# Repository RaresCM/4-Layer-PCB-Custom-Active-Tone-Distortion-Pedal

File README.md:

# Custom 4 Layer PCB Active Tone Distortion Pedal
Custom distortion pedal design aiming to apply theoretical knowledge from my EEE course to a real life project. Designed from the ground up from schematic to PCB to 3D model by me.

Implements my EEE course theory on filters, op-amps, power delivery and analog circuits.

## Specifications:
- 4 Layer PCB with a dedicated ground copper pour plane, power plane and 2 signal planes
- Dual 9V power input from a battery or barrel jack with ±9V delivery using a charge pump
- 3 Op-Amp design using a TL081 for gain and 2 NE5532 for volume output and 3 tone active tone stack
- De-coupling capacitors for stable op amp operation and a low pass filter input for noise elimination
- Designed in KiCad 10.0

## Repository Structure
- /manufacturing - KiCad generated gerber and manufacturing files
- /Distortion Pedal - KiCad files for the schematic, PCB layout, 3D model etc.
- /designlog - My design decisions and what could be improved

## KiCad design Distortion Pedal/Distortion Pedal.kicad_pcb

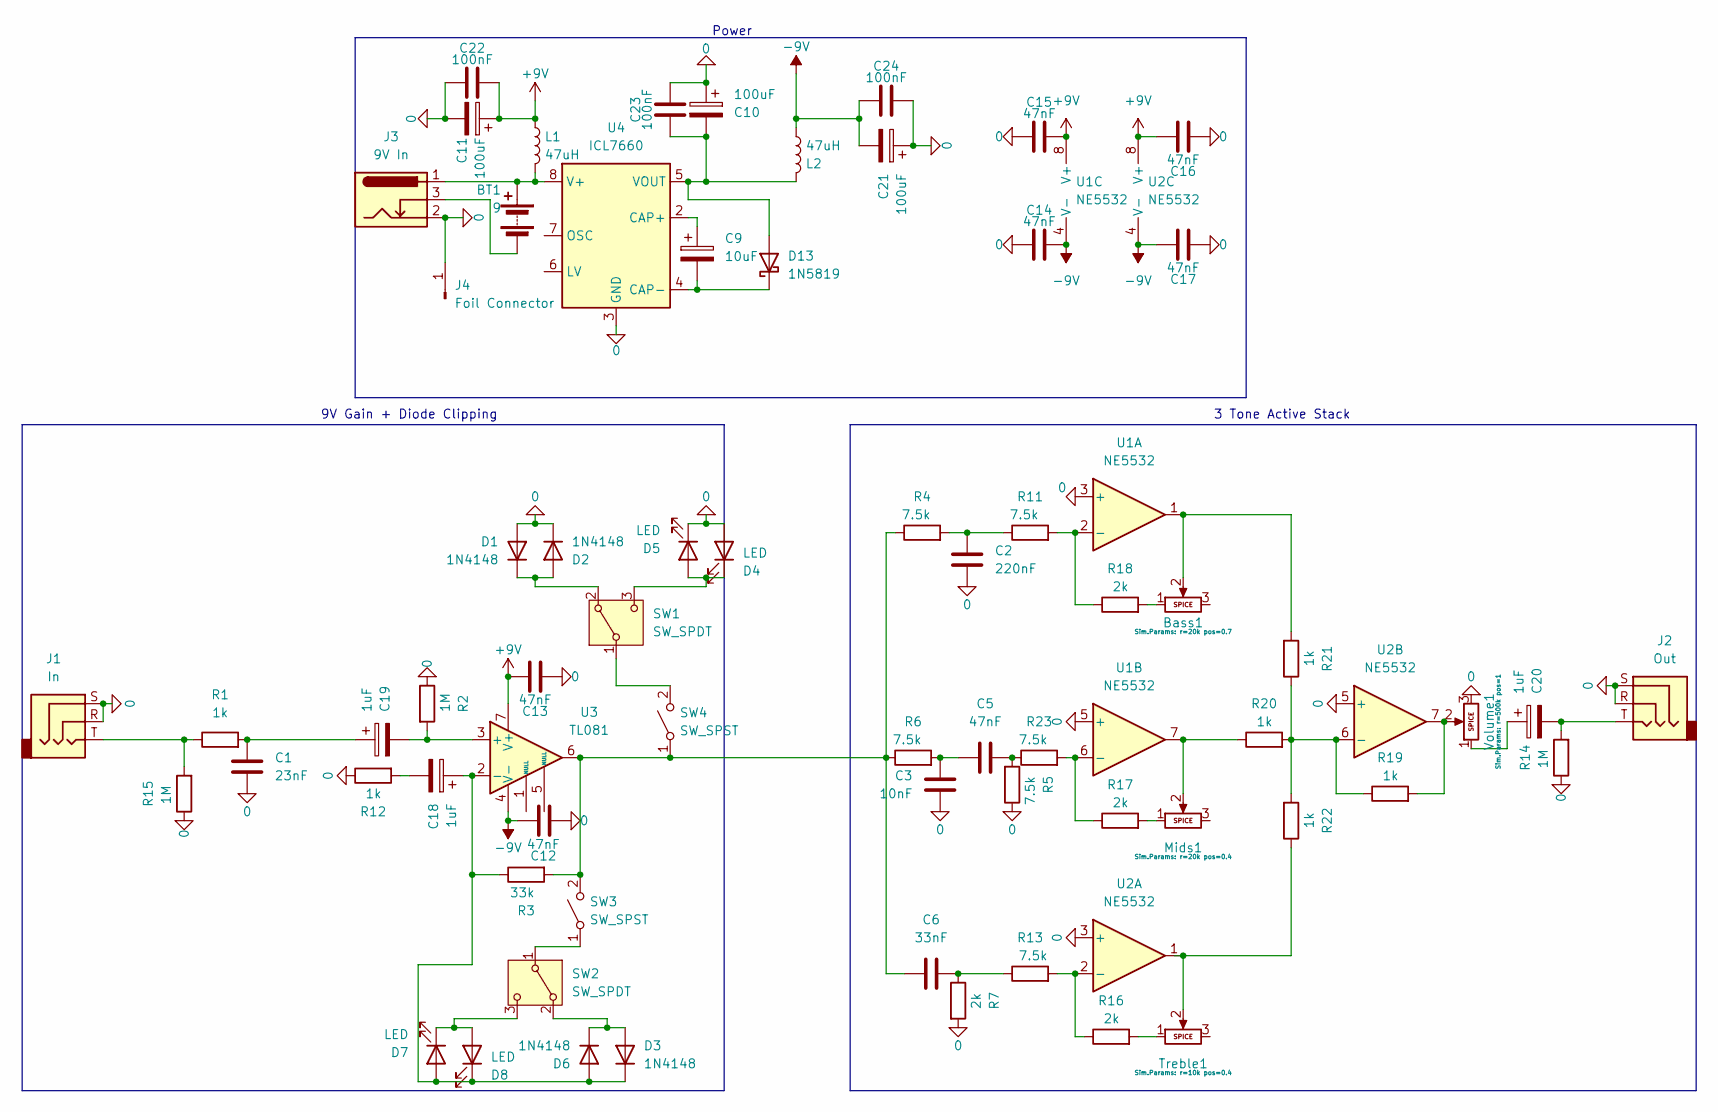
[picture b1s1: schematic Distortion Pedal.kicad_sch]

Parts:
BT1: 9; BatteryHolder_Eagle_12BH611-GR
Bass1: Potentiometer; Potentiometer_ACP_CA14V-15_Vertical
C1: 23nF; C_Disc_D11.0mm_W5.0mm_P7.50mm
C2: 220nF; C_Disc_D11.0mm_W5.0mm_P7.50mm
C3: 10nF; C_Disc_D11.0mm_W5.0mm_P7.50mm
C5, C12, C13, C14, C15, C16, C17: 47nF; C_Disc_D11.0mm_W5.0mm_P7.50mm
C6: 33nF; C_Disc_D11.0mm_W5.0mm_P7.50mm
C9: 10uF; CP_Radial_D14.0mm_P7.50mm
C10, C11, C21: 100uF; CP_Radial_D13.0mm_P7.50mm
C18, C19: 1uF; CP_Radial_D13.0mm_P7.50mm
C20: 1uF; CP_Radial_D14.0mm_P7.50mm
C22, C23, C24: 100nF; C_Disc_D11.0mm_W5.0mm_P7.50mm
D1, D2, D3, D6: 1N4148; D_DO-35_SOD27_P7.62mm_Horizontal
D4, D5, D7, D8: LED; LED_D5.0mm_FlatTop
D13: 1N5819; D_DO-41_SOD81_P10.16mm_Horizontal
J1: In; Jack_6.35mm_Neutrik_NJ3FD-V_Vertical
J2: Out; Jack_6.35mm_Neutrik_NJ3FD-V_Vertical
J3: 9V In; BarrelJack_GCT_DCJ200-10-A_Horizontal
J4: Foil Connector; PinHeader_1x01_P1.00mm_Vertical
L1, L2: 47uH; L_Radial_D12.0mm_P6.00mm_Murata_1900R
Mids1: Potentiometer; Potentiometer_ACP_CA14V-15_Vertical
R1, R12, R19, R20, R21, R22: 1k; R_Axial_DIN0204_L3.6mm_D1.6mm_P5.08mm_Horizontal
R2, R14, R15: 1M; R_Axial_DIN0204_L3.6mm_D1.6mm_P5.08mm_Horizontal
R3: 33k; R_Axial_DIN0204_L3.6mm_D1.6mm_P5.08mm_Horizontal
R4, R5, R6, R11, R13, R23: 7.5k; R_Axial_DIN0204_L3.6mm_D1.6mm_P5.08mm_Horizontal
R7, R16, R17, R18: 2k; R_Axial_DIN0204_L3.6mm_D1.6mm_P5.08mm_Horizontal
SW1, SW2: SW_SPDT; SW_Slide-03_Wuerth-WS-SLTV_10x2.5x6.4_P2.54mm
SW3, SW4: SW_SPST; SW_PUSH_1P1T_6x3.5mm_H5.0_APEM_MJTP1250
Treble1: Potentiometer; Potentiometer_ACP_CA14V-15_Vertical
U1, U2: NE5532; DIP-8_W7.62mm
U3: TL081; DIP-8_W7.62mm
U4: ICL7660; DIP-8_W7.62mm
Volume1: Potentiometer; Potentiometer_ACP_CA14V-15_Vertical

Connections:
0: C1.1, C2.1, C3.2, C10.1, C11.2, C12.2, C13.2, C14.2, C15.2, C16.2, C17.2, C21.1, C22.2, C23.1, C24.1, D1.2 (A), D2.1 (K), D4.2 (A), D5.1 (K), J1.R, J1.S, J2.R, J2.S, J3.2, J4.1 (Pin_1_1), R2.1, R5.1, R7.2, R12.1, R14.1, R15.1, U1.3 (+), U1.5 (+), U2.3 (+), U2.5 (+), U4.3 (GND), Volume1.3
+9V: C11.1, C13.1, C15.1, C16.1, C22.1, L1.1, U1.8 (V+), U2.8 (V+), U3.7 (V+)
-9V: C12.1, C14.1, C17.1, C21.2, C24.2, L2.2, U1.4 (V-), U2.4 (V-), U3.4 (V-)
unnamed: BT1.1 (+), J3.1, L1.2, U4.8 (V+)
unnamed: BT1.2 (-), J3.3
unnamed: Bass1.1, R18.2
unnamed: Bass1.2, R21.2, U1.1
unnamed: C1.2, C19.1, R1.2
unnamed: C2.2, R4.2, R11.1
unnamed: C3.1, C5.2, R6.2
unnamed: C5.1, R5.2, R23.1
unnamed: C6.1, R7.1, R13.1
unnamed: C18.2, R12.2
unnamed: C20.1, Volume1.1
unnamed: C20.2, J2.T, R14.2
unnamed: D1.1 (K), D2.2 (A), SW1.2 (B)
unnamed: D3.2 (A), D6.1 (K), SW2.2 (B)
unnamed: C18.1, D3.1 (K), D6.2 (A), D7.2 (A), D8.1 (K), R3.1, U3.2 (-)
unnamed: D4.1 (K), D5.2 (A), SW1.3 (C)
unnamed: D7.1 (K), D8.2 (A), SW2.3 (C)
unnamed: C10.2, C23.2, D13.2 (A), L2.1, U4.5 (VOUT)
unnamed: C9.2, D13.1 (K), U4.4 (CAP-)
unnamed: J1.T, R1.1, R15.2
unnamed: Mids1.1, R17.2
unnamed: Mids1.2, R20.1, U1.7
unnamed: R16.2, Treble1.1
unnamed: R19.2, U2.7, Volume1.2
unnamed: R22.1, Treble1.2, U2.1
unnamed: SW1.1 (A), SW4.2 (B)
unnamed: SW2.1 (A), SW3.1 (A)
unnamed: C6.2, R3.2, R4.1, R6.1, SW3.2 (B), SW4.1 (A), U3.6
unnamed: R11.2, R18.1, U1.2 (-)
unnamed: R17.1, R23.2, U1.6 (-)
unnamed: R13.2, R16.1, U2.2 (-)
unnamed: R19.1, R20.2, R21.1, R22.2, U2.6 (-)
unnamed: C19.2, R2.2, U3.3 (+)
unnamed: C9.1, U4.2 (CAP+)

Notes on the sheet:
3 Tone Active Stack
Power
9V Gain + Diode Clipping

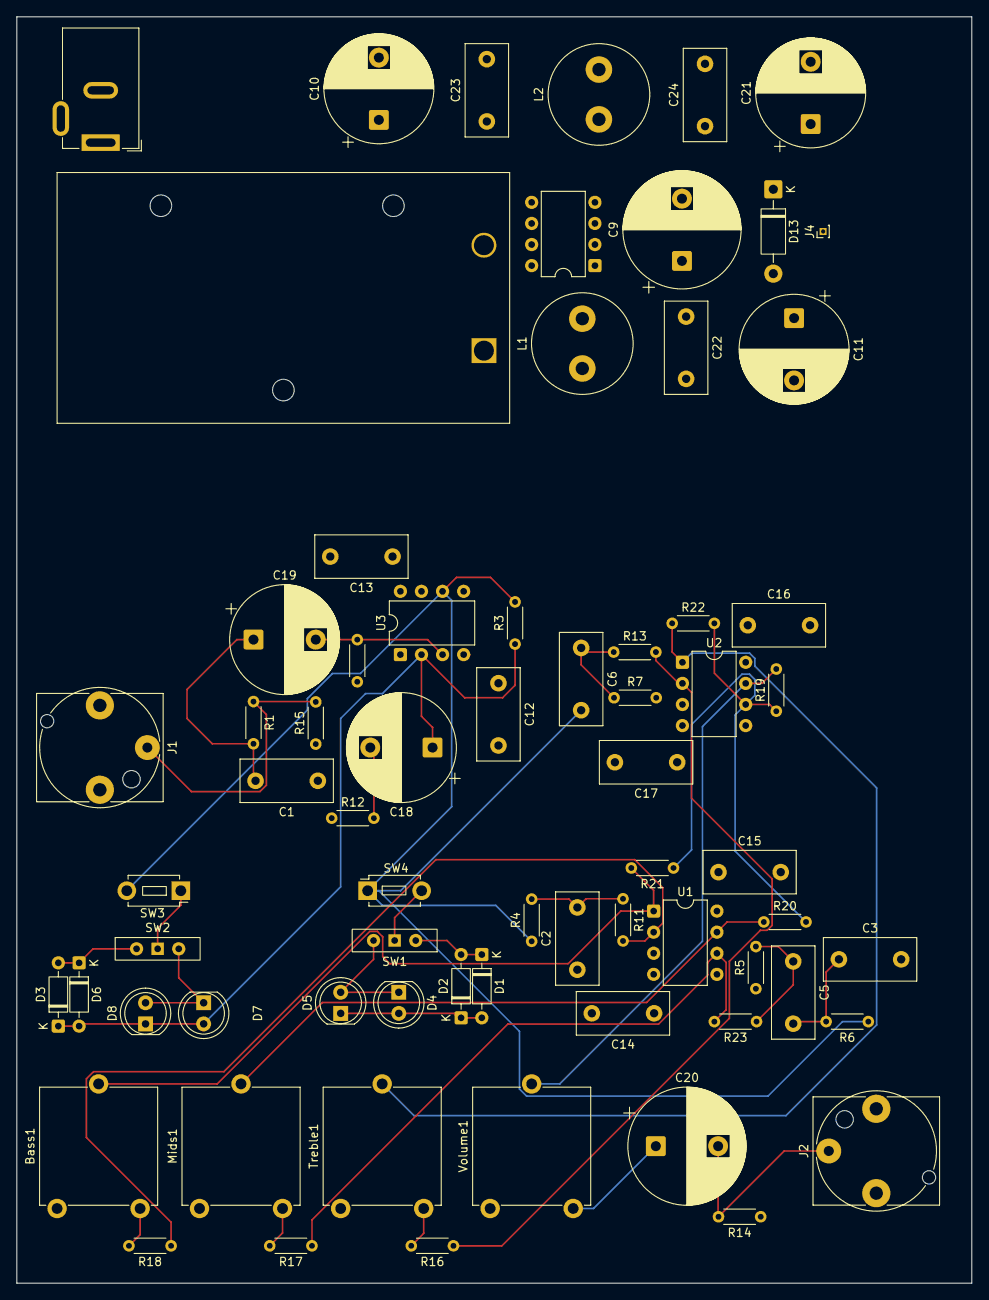
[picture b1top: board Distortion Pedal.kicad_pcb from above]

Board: 4 copper layers, 115.0 x 152.5 mm, 69 parts (0 on the bottom side), 37 nets.
